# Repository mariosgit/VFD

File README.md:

# VFD

A collection of upcycling projects for Vakuum Fluorescent Displays (VFD). These are Display as you may find in Audio/Video gear like CD/DVD players. A VFD requires high voltage to control anodes and gates, and a small AC voltage for the fillament(heater). To drive each single display element, a time multiplexed controller is required.

## Project Structure...

This is a playground for testing VFDs and there are the PCBs in PCB-KiCAD. See below..

If you only want the display drivers, check out the external repos which are submoduled in the ```./lib``` folder.

```lib/...``` containes submodule display libs and maybe some other local libs which are in development. If a stable status is reached I move them into their own repo.

```src/VFD_TPIC..``` stuff was not integrated into this platformio project yet..

```src/PanelDemo``` is a simple example for a VFD + encoder and button inputs.

```src/FreeDSPController``` is like PanelDemo + it reads some data via I2C from a FreeDSP/ADSP1701. It's a first experiment to use the code generated by SigmaStudio.

### Software Testing

So this is "just" a wrapper PlatformIO project which allows quick switching between the displays I work on.

The thing to be build can be choosen in ```.env``` file. If there is none, copy the ```.env.example```.

### src/main

Is a wrapper into the other sources under ```src``` or into the examples under ```lib/XYZ/examples/...```.

You can also switch between demo programms by commenting in/out the defines.. only one at a time... but using ```.env``` does not infect the git repo.

## PCBs

There are some sub-schematics like VFD-Power which are included in the other schematics.

### MN12832JC-TeensyLC

This is a VFD + 2 Encoders + 2 Switches. (For the FreeDSPController)

Status: Works somewhat, It would have been better with Level shifters. During power up it can show some random noise, due to level issues.

### GP1294AI

This is a board with the VFD + 2 encoders + 10 switches.

#### Status: Experimental, PCB is in development. 

Has some bugs, I2C and I2S on wrong pins... etc.

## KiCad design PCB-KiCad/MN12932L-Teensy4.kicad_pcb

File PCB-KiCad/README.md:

# PCB's

### Reminder

To edit a schematic/pcb, open the .pro file first (double click) KiCad needs this to handle sch/pcb together, otherwise u get wiered errors when updating pcb from schematic.

## GP1294 panel

| front | back |
|---|---|
|  |  |
| | |

A Panel with that display and an Teensy4.

Intended Use: Graphical EQ. The bottom PCB is a FreeDSP-AllInOne.
 * Infopage https://freedsp.github.io/
 * Github: https://github.com/freeDSP/freeDSP-ALLinONE 

Contains
* Power for VFD (~3V fillament, 30-50V for anode and grid) and 5V for other stuff.
* Teensy4 - Controls the Amp and shows vintage spectrum analyser.
* 2 Encoders
* 5 Buttons.

### Status

Tested, has bugs... Can be patched to work somewhat.

### Bugs

* VFD pin 9 (TEST) must have 100k pullup to 3.3V and small buffer C.✅
* SDA/SCL are twisted ! ✅
* PL(atch) is not connected to ATTiny ! Removed ATTiny ✅
* ATTiny fliegt raus, zu umstaendlich.✅
* I2S pins wrong, fixed + SRCs ✅
* 5V reg wrong footprint (from a kicad lib)
* Add revision info
* Crosscheck wiring with proto

### Bugs

* RECOM 5V reg wrong footprint (from a kicad lib)
* VFD pin 9 (TEST) must have 100k pullup to 3.3V and small buffer C.

### Todo

* Test audio connection to/from teensy I2S slave ! Can it do USB playback ? T3.2 or T4.0 ?

* FreeDSP-AIO flaws ✅
  * speaker mute before shutdown...
    * it has a startup unmute circuit but no shutdown...
    * [One more7414 gate and 2 diodes and 2 resistors...](https://www.falstad.com/circuit/circuitjs.html?ctz=CQAgjCAMB0l3BWEAmM0EE4DMGAcB2ZLMSANjABYxkQFTbbJaBTAWjDACgA3EV-XBXCkmrQbmFMmEElOgQpUdJwBKfcZPUZ6YEVHAppNavpgJOAB3W6UyIWJvJcErKc5hcr1lgTH89VmRCcH9TdHBoUnosaCxXJEh3Tz4fGm0+ILT6OSQ0KJAYuIZEjy9UkAo4DODKxTMI-ML4qE4Adz4wUJt2ExtE9sC7YQ6u7M4AcxH6XFFO+nSpTgBjKeH2UJn9ZDYJCmgMbREOHAO8SgTYSC4AJ1XWCgl1nWzweDg21bn1aVDE26eQgEvnZFLJ4MtViDVlhIEImNsxBV9rgMP4sKQMHRILhkNglHAuJMATD7F8sMg6h9BkIoQCof1IZUOiZ6VSvl9AsEvgzqWtyn0qfyAuUFpZqjRauKKqQhK5FlYehKqorpbK3ANMiB0pzjE4WhquXrvL5wHqefyjfzflTkENaeVWQMHUzjUrFhT8B16JKmHFvSAALYAVwALsxOB6pRyKRJKEIhABBAMWVgAegAogA5COQT0OZ6iZxMB4VEAANQAlgA7AAU1ECFDLAEoc3nCPCXaQhhwJYGAIYWAA6AGdh0GLBYADYATxHZZHIYA9iOEGWqbhHEN85o-nx2ygXfuSfoZu8iUfYXuKQVr4sBvvaaQ6Af5Xwn-RH8-j3KWqU+AhQlpCh0npJRckiaJYmaHkH2xK8O1fe4QJdYDvSqH8eVtWVL2JS9MLtYJeVZP97nJPgS1dciJByBpIKKBIxRVWkewKS8MMFE17keDkSx5CgyKAsiuP1O5qG40JhMSAATKVJXYDA3RQEApOYAAzPsg0nENOBknUKm1MAFP0j9lLUjStLZEw5MMxSeRsiplXs1CRNIiVtX4mhWQVGUqLfWUaHYgYfOEgFJNbUSjQo3RixAAAFRdWmYa4AHkq3CyiQuPVh0iEAArINhxDEc+xHAALZhJwsJKF2XYdxmYIrh1XdKAI-F1fFjUIhArAMA2YKSKz7MMRwsBLquHKSEqrEcVLDJYQwrRc0sjeS3ICTYEAoeMQGSlQR0XVSRrG65JtaabhwAHyOxLrnHdKeMeTZsv9YdJwS67xvHGaGuYebFrS-53xff9AKZaRwQGZzBM8sH3C7L0HNmb1NhoFT1M0kNWEnfqDAUfFCQRh4keMtx-hsayrKqJgEHeSGyOcvTnJg68WP4QRwBMGD2dZgQhGi398HsfcedIWMjIgGn4HxDAqDeOX4BoFRmGHCtCr7KslnDe9Rc0Nm+b0RJF0MG99AADw3K4aAuPGkCQCRUH0JBWE22gbelJTwdoALqIYQIsE4I2KACmgmHNkgWTkGRSwSAoY4ge4JR-J36dcOVYAYoA) ... voltage divider at the schmitt input set to trigger when Vin goes below 8V or so !? then OR that output via 2 diodes into the spk_sleep. Adjust: turn pot from full (cw) towards 0 (ccw) until the mute LED goes off.
    * tested ✅
  * Not much capacitance at Vin, more caps ! Could delay the shutdown ! More time to mute ! ✅

## MN12832L panel

| front | back |
|---|---|
|  |  |
| | |

Eurorack 24U format - 12cm width. Made for some very specific recycled receiver knobs.

### Status

Batch v0.1 ordered.

### BOM

| "Id" | "Designator" | "Footprint" | "Quantity" | "Designation" |
| --- | --- | --- | --- | --- |
| 15 | "U3,U4" | "SOIC-16_3.9x9.9mm_P1.27mm" | 2 | "74HC165" |  |  | 
| 34 | "U1" | "MN12832L" | 1 | "~" |  |  | 
| 30 | "U2" | "Teensy4.0" | 1 | "~" |  |  | 
| 23 | "U5" | "Converter_DCDC_RECOM_R-78E-0.5_THT" | 1 | "R-78B5.0-2.0" |  |  | 
| 29 | "IC2" | "SO8" | 1 | "ZXBM5210" |  |  | 
| 17 | "IC1" | "SO14" | 1 | "74132D" |  |  | 
| 18 | "IC3" | "TO263-5" | 1 | "XL6009" |  |  | 
|  2 | "D5,D4,D3,D2" | "D_SOD-123" | 4 | "1N4448W" |  |  | 
| 16 | "D1" | "D_SOD-123" | 1 | "1N5818" |  |  | 
| 14 | "L1" | "L_Cenker_CKCS5020" | 1 | "SM-NE45" |  |  | 
| 22 | "L2" | "L_Cenker_CKCS8040" | 1 | "22uH" |  |  | 
|  1 | "C1" | "C1206" | 1 | "4.7n" (FF-Freq) |  |  | 
| 10 | "C4" | "CP_Elec_6.3x5.8" | 1 | "47u/35v" |  |  | 
| 12 | "C6" | "CP_Elec_6.3x5.8" | 1 | "4.7u/100v" |  |  | 
| 13 | "C3,C5" | "C_1210_3225Metric_Pad1.33x2.70mm" | 2 | "1u/100v" |  |  | 
| 33 | "C2" | "C_0603_1608Metric_Pad1.08x0.95mm" | 1 | "1u" |  |  | 
|  4 | "R2,R1" | "R_0603_1608Metric_Pad0.98x0.95mm" | 2 | "2.7k" (R2-FF-Freq) |  |  | 
|  5 | "RN4,RN3,RN1,RN2" | "R_Array_SIP5" | 4 | "R_Network04" |  |  | 
| 25 | "R14,R13" | "R_0603_1608Metric" | 2 | "2.2k" |  |  | 
| 11 | "R6" | "R_Axial 10mm" | 1 | "91k" |  |  | 
| 24 | "R4" | "R_Axial_DIN0207_L6.3mm_D2.5mm_P10.16mm" | 1 | "91k" VoltReg |  |  | 
| 31 | "R5" | "R_Axial_DIN0207_L6.3mm_D2.5mm_P10.16mm" | 1 | "2k" | |  | 
|  9 | "R3" | "0411_15" | 1 | "22" 5W |  |  | 
| 35 | "SW3,SW2,SW1,SW4,SW5" | "RotaryEncoder_Alps_EC11E" | 5 |  |  |  | 

# Refs

Used Kicad 3d models:
 * models https://gitlab.com/MountyRox/kicad-packages3D.git 
 * sources https://gitlab.com/kicad/libraries/kicad-packages3D-source.git

# Reminders

Start more Kicad instances on MacOS:
```
open -n -a "kicad"
```

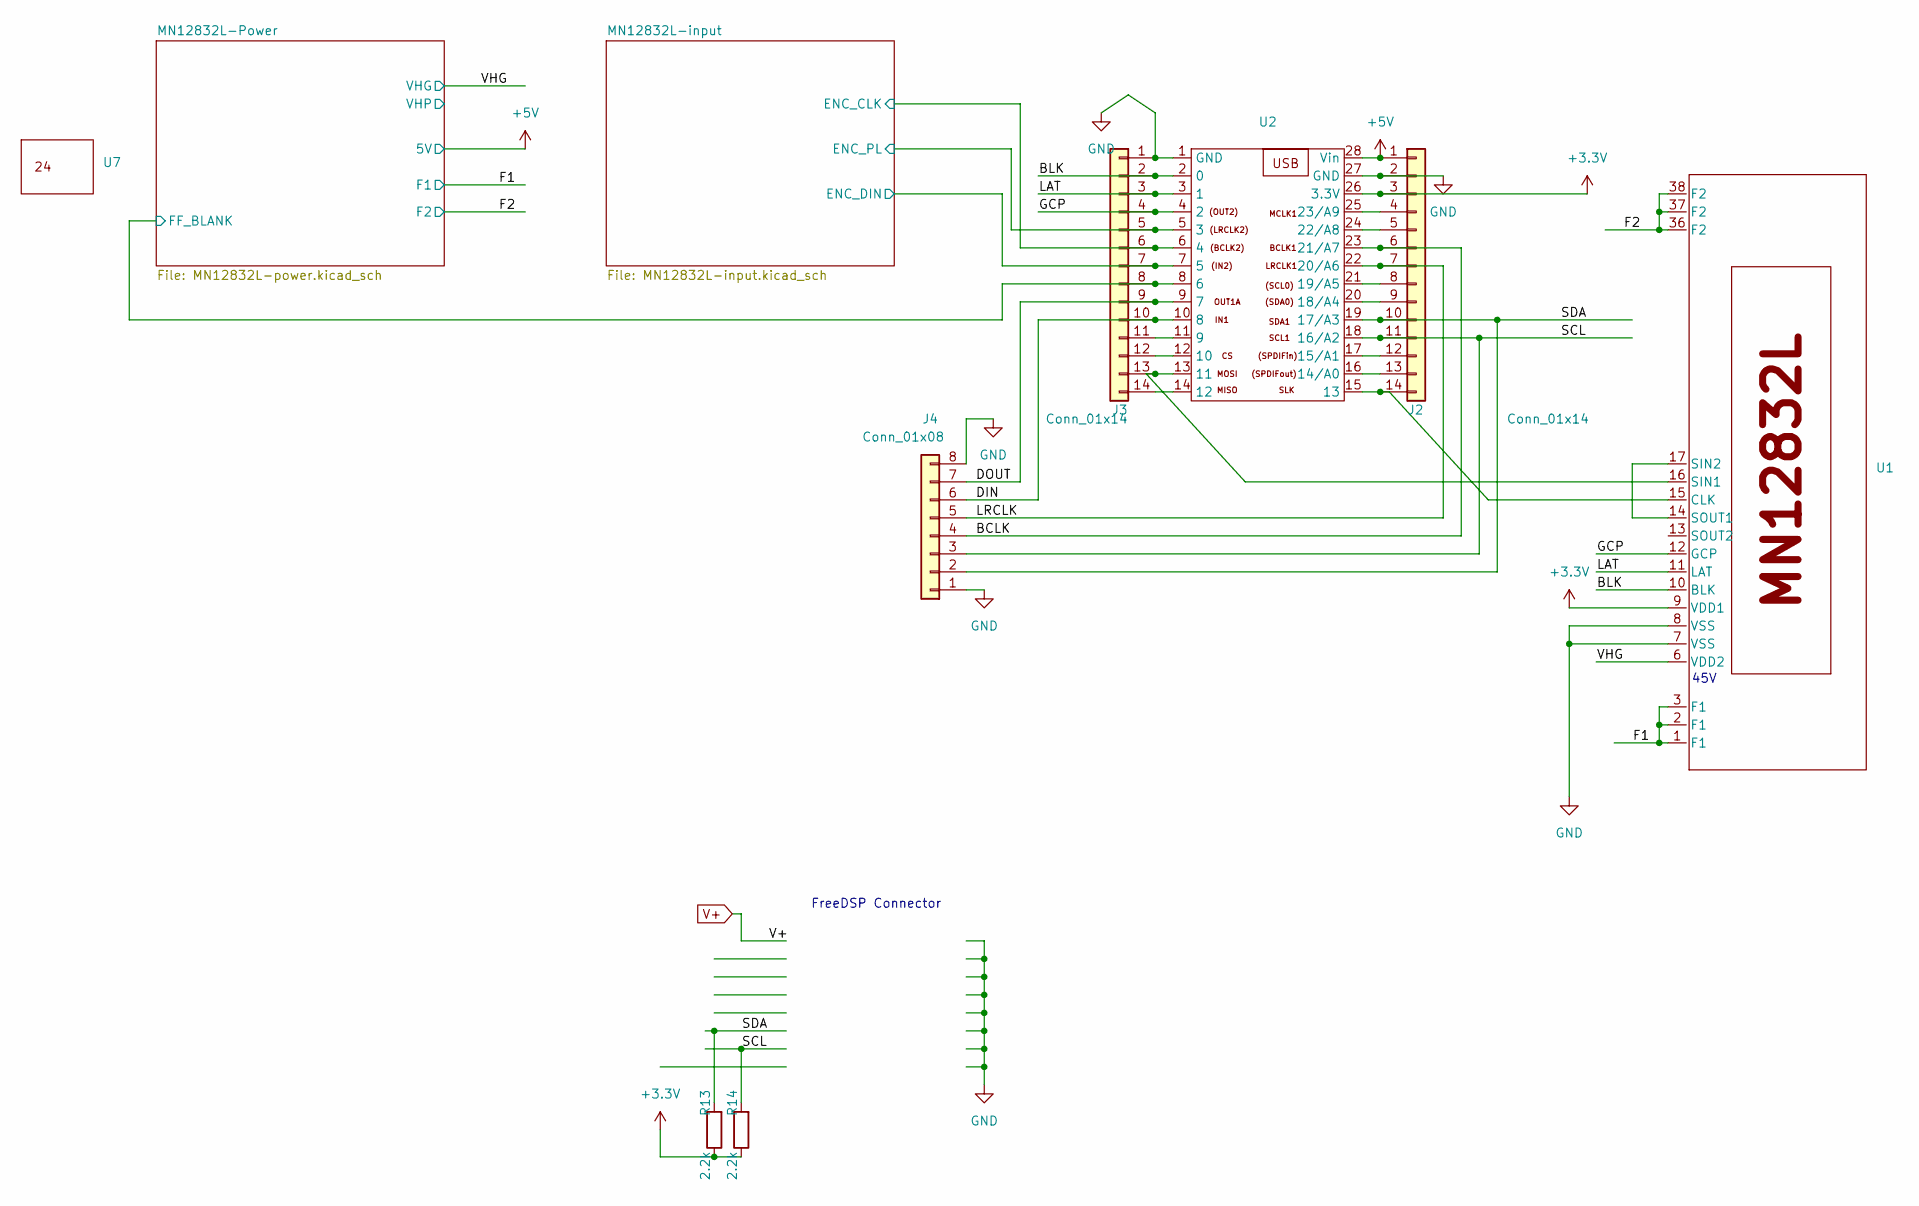
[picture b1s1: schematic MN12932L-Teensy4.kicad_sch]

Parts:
J2, J3: Conn_01x14; PinSocket_1x14_P2.54mm_Vertical
J4: Conn_01x08; PinSocket_1x08_P2.54mm_Vertical
R13, R14: 2.2k; R_0603_1608Metric
U1: MN12832L
U2: Teensy4.0
U7: MN12832L-Front24

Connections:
+3.3V: J2.3, R13.1, R14.1, U1.9 (VDD1), U2.26 (3.3V); also elsewhere on the board
+5V: J2.1, U2.28 (Vin); also elsewhere on the board
/BCLK: J2.6, J4.4, U2.23 (21/A7)
/BLK: J3.2, U1.10 (BLK), U2.2 (0)
/DIN: J3.10, J4.6, U2.10 (8)
/DOUT: J3.9, J4.7, U2.9 (7)
/GCP: J3.4, U1.12 (GCP), U2.4 (2)
/LAT: J3.3, U1.11 (LAT), U2.3 (1)
/LRCLK: J2.7, J4.5, U2.22 (20/A6)
/MN12832L-input/ENC_CLK: J3.6, U2.6 (4); also elsewhere on the board
/MN12832L-input/ENC_DIN: J3.7, U2.7 (5); also elsewhere on the board
/MN12832L-input/ENC_PL: J3.5, U2.5 (3); also elsewhere on the board
/SCL: J2.11, J4.3, R14.2, U2.18 (16/A2)
/SDA: J2.10, J4.2, R13.2, U2.19 (17/A3)
F1: U1.1 (F1), U1.2 (F1), U1.3 (F1); also elsewhere on the board
F2: U1.36 (F2), U1.37 (F2), U1.38 (F2); also elsewhere on the board
FF_BLANK: J3.8, U2.8 (6); also elsewhere on the board
GND: J2.2, J3.1, J4.1, J4.8, U1.7 (VSS), U1.8 (VSS), U2.1 (GND), U2.27 (GND); also elsewhere on the board
unnamed: J2.4, U2.25 (23/A9)
unnamed: J2.5, U2.24 (22/A8)
unnamed: J2.8, U2.21 (19/A5)
unnamed: J2.9, U2.20 (18/A4)
unnamed: J2.12, U2.17 (15/A1)
unnamed: J2.13, U2.16 (14/A0)
unnamed: J2.14, U1.15 (CLK), U2.15 (13)
unnamed: J3.11, U2.11 (9)
unnamed: J3.12, U2.12 (10)
unnamed: J3.13, U1.16 (SIN1), U2.13 (11)
unnamed: J3.14, U2.14 (12)
unnamed: U1.14 (SOUT1), U1.17 (SIN2)
VHG: U1.6 (VDD2); also elsewhere on the board

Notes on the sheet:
FreeDSP Connector
45V

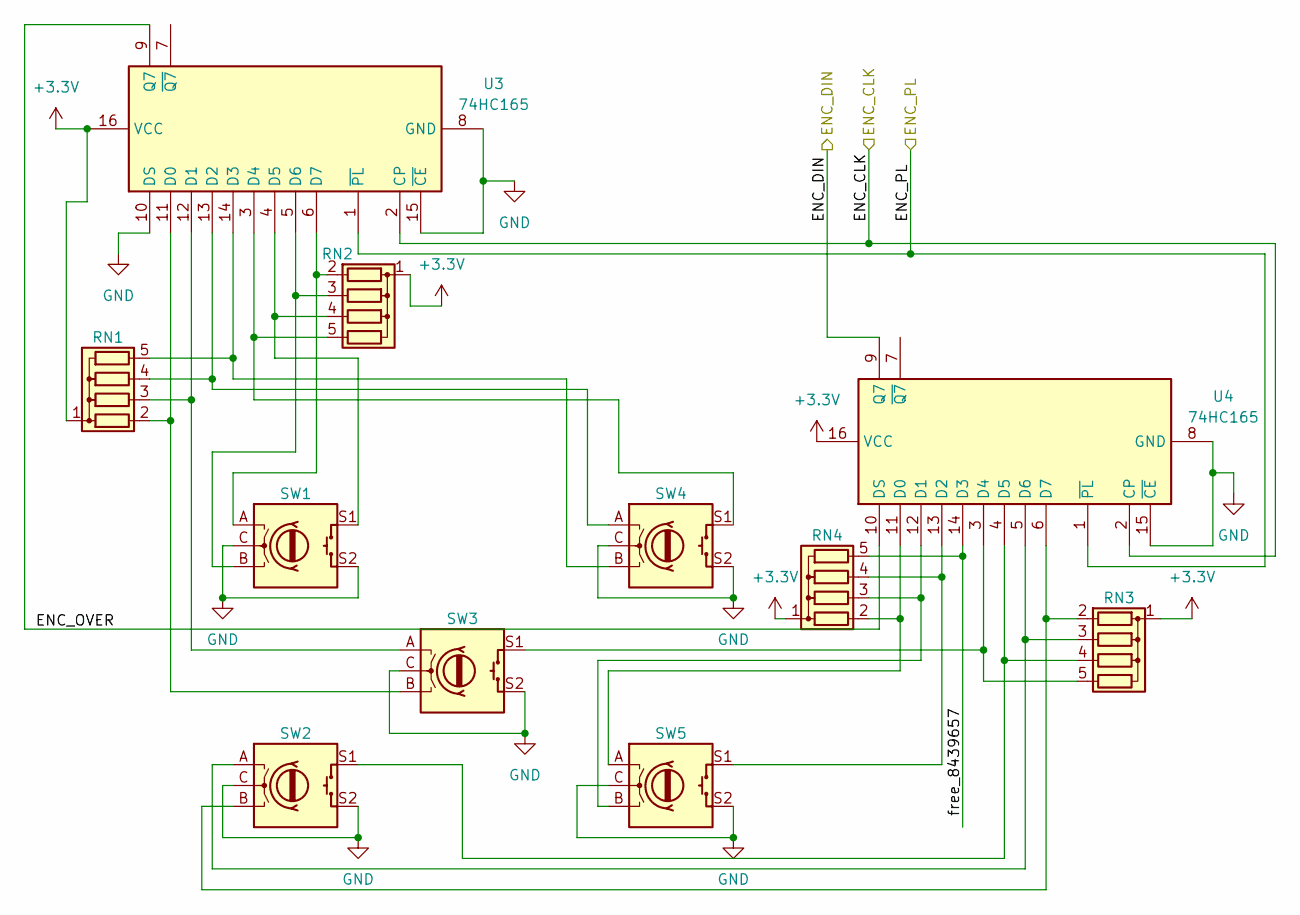
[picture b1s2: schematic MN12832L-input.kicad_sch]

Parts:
RN1, RN2, RN3, RN4: R_Network04; R_Array_SIP5
SW1, SW2, SW3, SW4, SW5: RotaryEncoder_Switch; RotaryEncoder_Alps_EC11E-Switch_Vertical_Centered
U3, U4: 74HC165; SOIC-16_3.9x9.9mm_P1.27mm

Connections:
+3.3V: RN1.1 (common), RN2.1 (common), RN3.1 (common), RN4.1 (common), U3.16 (VCC), U4.16 (VCC); also elsewhere on the board
/MN12832L-input/ENC_CLK: U3.2 (CP), U4.2 (CP); also elsewhere on the board
/MN12832L-input/ENC_DIN: U4.9 (Q7); also elsewhere on the board
/MN12832L-input/ENC_OVER: U3.9 (Q7), U4.10 (DS)
/MN12832L-input/ENC_PL: U3.1 (~PL), U4.1 (~PL); also elsewhere on the board
/MN12832L-input/free_8439657: RN4.5 (R4), U4.14 (D3)
GND: SW1.C, SW1.S2, SW2.C, SW2.S2, SW3.C, SW3.S2, SW4.C, SW4.S2, SW5.C, SW5.S2, U3.8 (GND), U3.10 (DS), U3.15 (~CE), U4.8 (GND), U4.15 (~CE); also elsewhere on the board
unnamed: RN1.2 (R1), SW3.B, U3.11 (D0)
unnamed: RN1.3 (R2), SW3.A, U3.12 (D1)
unnamed: RN1.4 (R3), SW4.A, U3.13 (D2)
unnamed: RN1.5 (R4), SW4.B, U3.14 (D3)
unnamed: RN2.2 (R1), SW1.A, U3.6 (D7)
unnamed: RN2.3 (R2), SW1.B, U3.5 (D6)
unnamed: RN2.4 (R3), SW1.S1, U3.4 (D5)
unnamed: RN2.5 (R4), SW4.S1, U3.3 (D4)
unnamed: RN3.2 (R1), SW2.B, U4.6 (D7)
unnamed: RN3.3 (R2), SW2.A, U4.5 (D6)
unnamed: RN3.4 (R3), SW2.S1, U4.4 (D5)
unnamed: RN3.5 (R4), SW3.S1, U4.3 (D4)
unnamed: RN4.2 (R1), SW5.A, U4.11 (D0)
unnamed: RN4.3 (R2), SW5.B, U4.12 (D1)
unnamed: RN4.4 (R3), SW5.S1, U4.13 (D2)

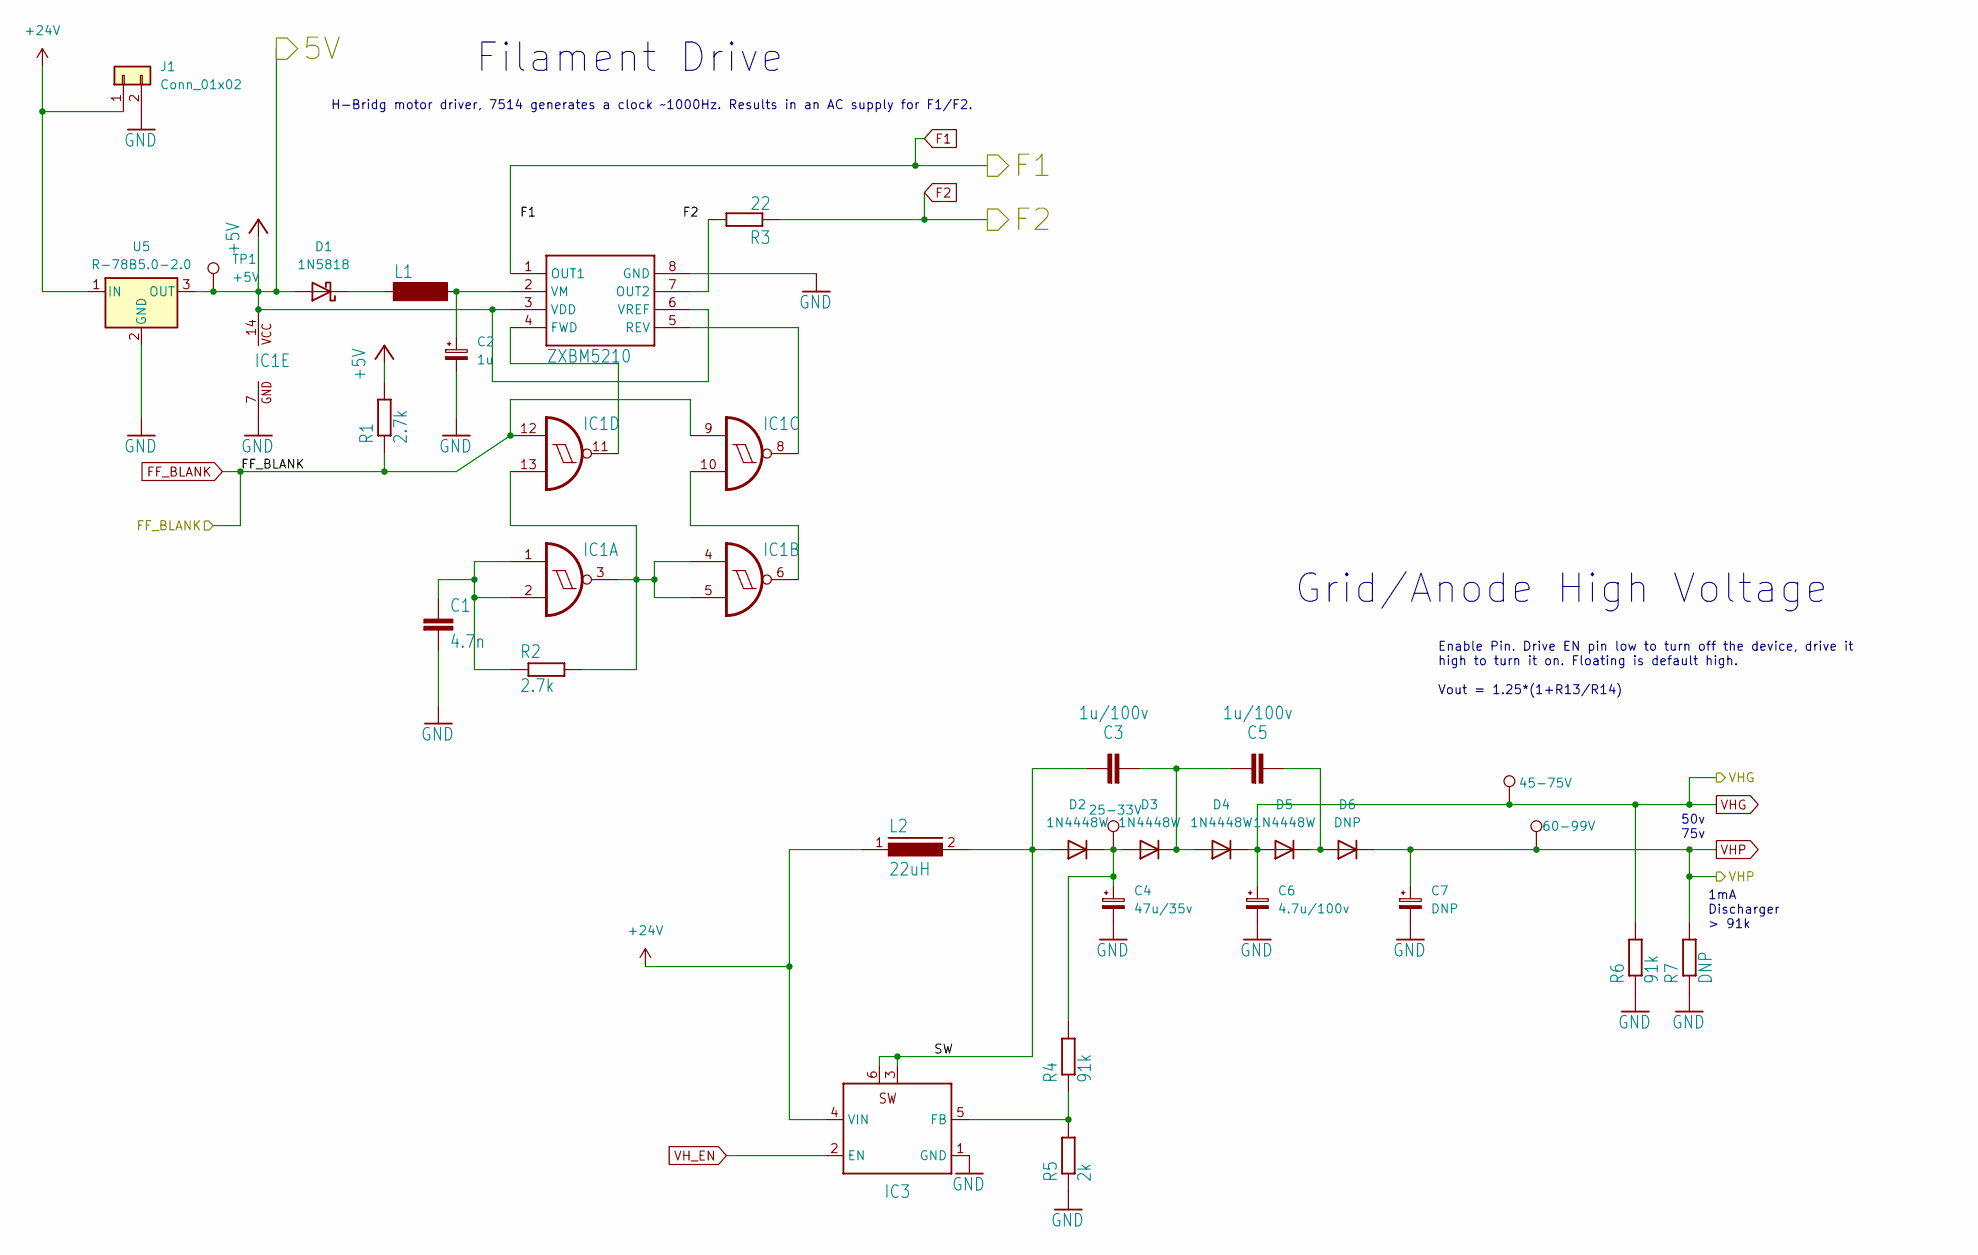
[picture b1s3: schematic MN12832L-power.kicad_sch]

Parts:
C1: 4.7n; C1206
C2: 1u; C_0603_1608Metric_Pad1.08x0.95mm_HandSolder
C3, C5: 1u/100v; C_1210_3225Metric_Pad1.33x2.70mm_HandSolder
C4: 47u/35v; CP_Elec_6.3x5.8
C6: 4.7u/100v; CP_Elec_6.3x5.8
C7: DNP; CP_Elec_6.3x5.8
D1: 1N5818; D_SOD-123
D2, D3, D4, D5: 1N4448W; D_SOD-123
D6: DNP; D_SOD-123
IC1: 74132D; SO14
IC2: ZXBM5210; SO8
IC3: TO263-5
J1: Conn_01x02; TerminalBlock_Phoenix_MKDS-1,5-2-5.08_1x02_P5.08mm_Horizont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
L1: SM-NE45; L_Cenker_CKCS5020
L2: 22uH; L_Cenker_CKCS8040
R1, R2: 2.7k; R_0603_1608Metric_Pad0.98x0.95mm_HandSolder
R3: 22; 0411_15
R4: 91k; R_Axial_DIN0207_L6.3mm_D2.5mm_P10.16mm_Horizontal
R5: 2k; R_Axial_DIN0207_L6.3mm_D2.5mm_P10.16mm_Horizontal
R6: 91k; R_0603_1608Metric_Pad0.98x0.95mm_HandSolder
R7: DNP; R_0603_1608Metric_Pad0.98x0.95mm_HandSolder
TP1: +5V; TestPoint_Pad_2.0x2.0mm
TP2: 25-33V; TestPoint_Pad_2.0x2.0mm
TP3: 45-75V; TestPoint_Pad_2.0x2.0mm
TP4: 60-99V; TestPoint_Pad_2.0x2.0mm
U5: R-78B5.0-2.0; Converter_DCDC_RECOM_R-78E-0.5_THT

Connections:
+5V: D1.2 (A), IC1.14 (VCC), IC2.3 (VDD), IC2.6 (VREF), R1.2, TP1.1, U5.3 (OUT); also elsewhere on the board
+24V: IC3.4 (VIN), J1.1, L2.1, U5.1 (IN)
/MN12832L-Power/SW: C3.1, D2.2 (A), IC3.3 (SW), IC3.6 (SW@1), L2.2
F1: IC2.1 (OUT1); also elsewhere on the board
F2: R3.1; also elsewhere on the board
FF_BLANK: IC1.9 (I0), IC1.12 (I0), R1.1; also elsewhere on the board
GND: C1.2, C2.2, C4.2, C6.2, C7.2, IC1.7 (GND), IC2.8 (GND), IC3.1 (GND), J1.2, R5.1, R6.1, R7.1, U5.2 (GND); also elsewhere on the board
unnamed: D1.1 (K), L1.1
unnamed: C4.1, D2.1 (K), D3.2 (A), R4.2, TP2.1
unnamed: C3.2, C5.1, D3.1 (K), D4.2 (A)
unnamed: C5.2, D5.1 (K), D6.2 (A)
unnamed: C1.1, IC1.1 (I0), IC1.2 (I1), R2.1
unnamed: IC1.3 (O), IC1.4 (I0), IC1.5 (I1), IC1.13 (I1), R2.2
unnamed: IC1.6 (O), IC1.10 (I1)
unnamed: IC1.8 (O), IC2.5 (REV)
unnamed: IC1.11 (O), IC2.4 (FWD)
unnamed: IC2.7 (OUT2), R3.2
unnamed: C2.1, IC2.2 (VM), L1.2
unnamed: IC3.5 (FB), R4.1, R5.2
VHG: C6.1, D4.1 (K), D5.2 (A), R6.2, TP3.1; also elsewhere on the board
VHP: C7.1, D6.1 (K), R7.2, TP4.1
VH_EN: IC3.2 (EN)

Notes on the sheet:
H-Bridg motor driver, 7514 generates a clock ~1000Hz. Results in an AC supply for F1/F2.
Filament Drive
50v 75v
Grid/Anode High Voltage
Enable Pin. Drive EN pin low to turn off the device, drive it high to turn it on. Floating is default high. Vout = 1.25*(1+R13/R14)
1mA Discharger > 91k

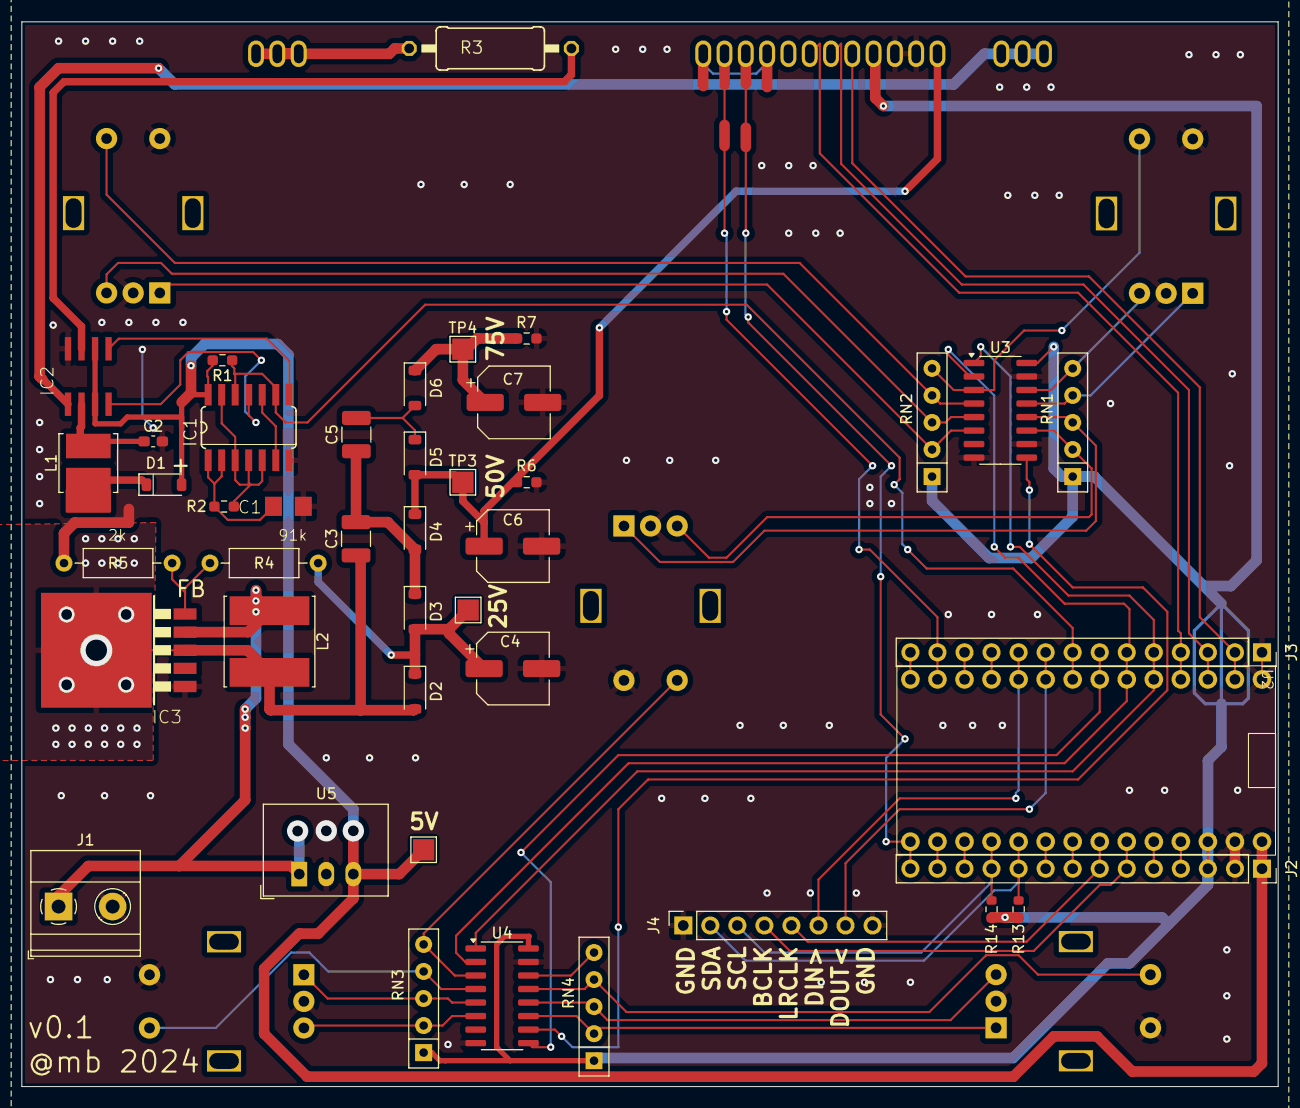
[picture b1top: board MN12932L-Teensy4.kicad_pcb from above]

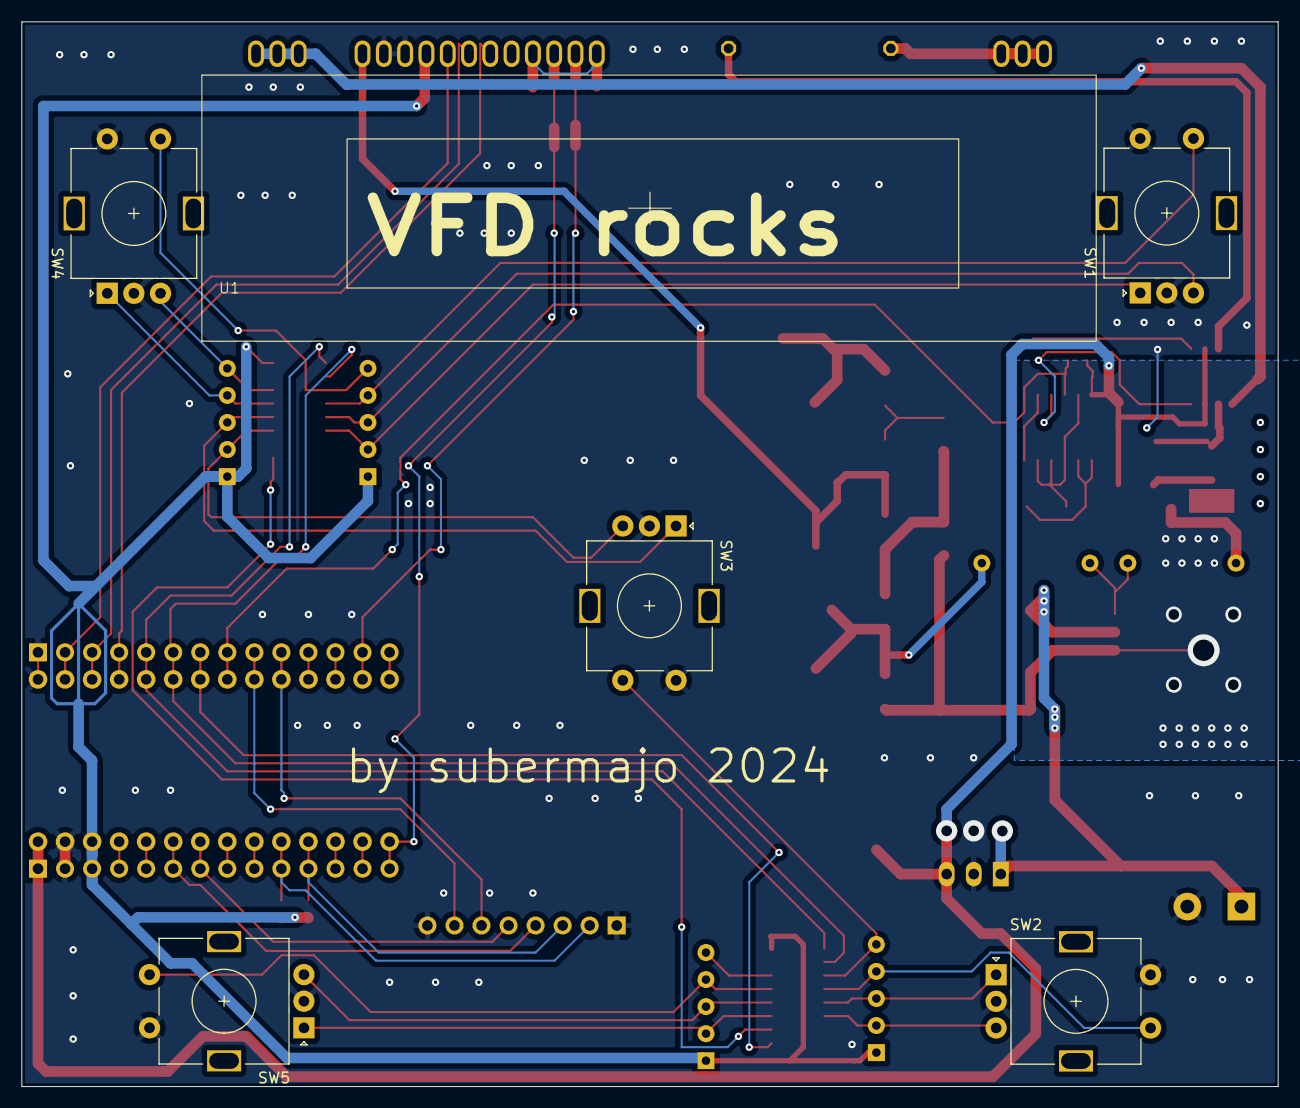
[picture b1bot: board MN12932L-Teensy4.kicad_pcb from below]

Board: 2 copper layers, 118.0 x 100.0 mm, 50 parts (6 on the bottom side), 63 nets.

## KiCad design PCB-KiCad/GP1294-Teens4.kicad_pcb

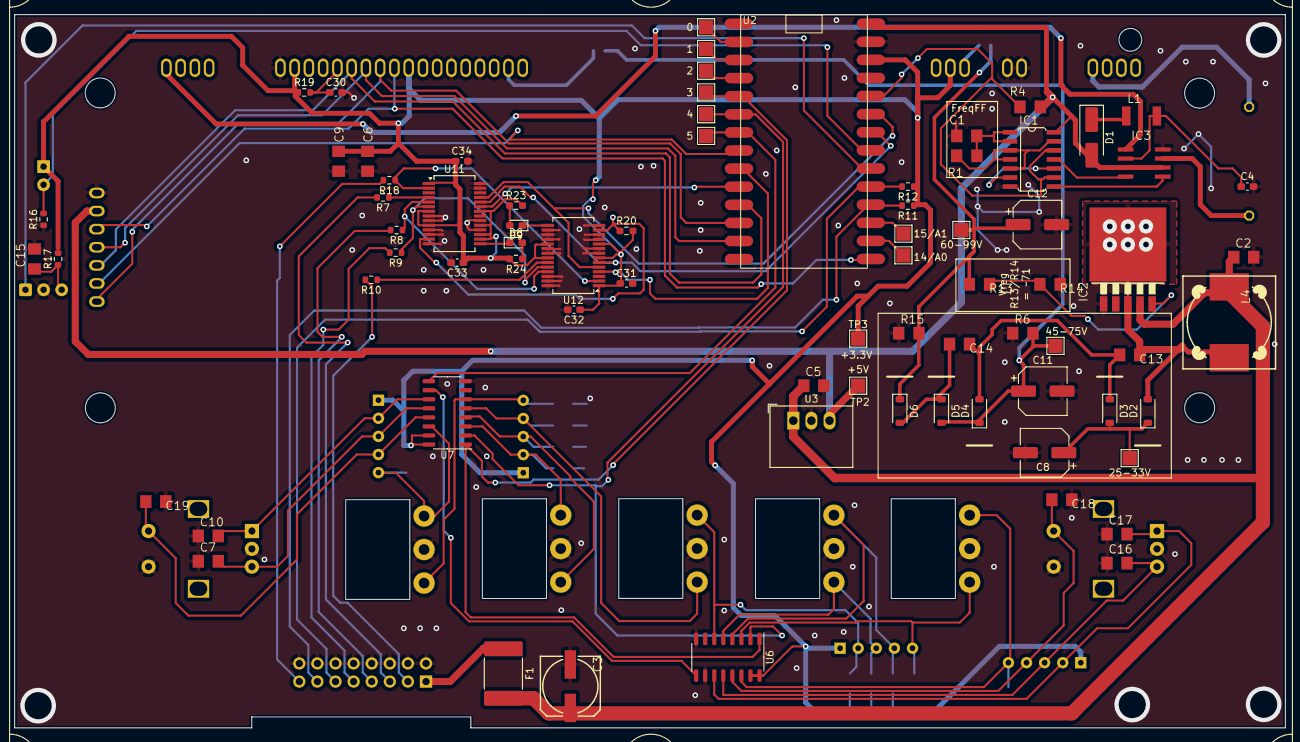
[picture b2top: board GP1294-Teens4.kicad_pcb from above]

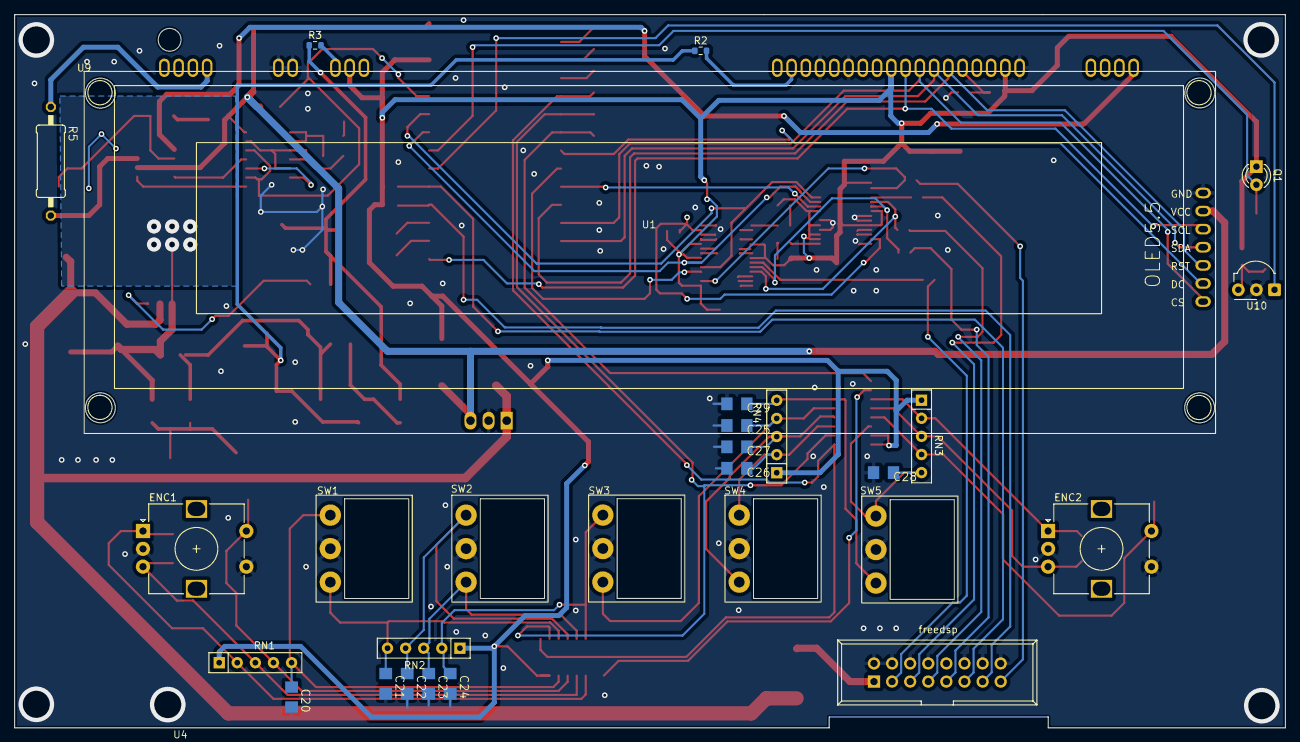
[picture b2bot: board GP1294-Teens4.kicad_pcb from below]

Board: 2 copper layers, 178.3 x 100.1 mm, 106 parts (29 on the bottom side), 80 nets.

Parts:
C1: 4.7n; C1206
C2, C6, C15: 100n; C1206
C3: 10u; 153CLV-0807
C4: 1u; C_0603_1608Metric_Pad1.08x0.95mm_HandSolder
C5: C-EUC1206; C1206
C7, C10, C16, C17, C18, C19, C20, C21, C22, C23, C24, C25, C26, C27, C28, C29: 10n; C1206
C8: 47u/35v; CP_Elec_6.3x5.8
C9: 1u; C1206
C11, C12: 4.7u/100v; CP_Elec_6.3x5.8
C13, C14: 1u/100v; C1206
C30, C31, C33: 100n; C_0603_1608Metric_Pad1.08x0.95mm_HandSolder
C32, C34: 10u; C_0603_1608Metric_Pad1.08x0.95mm_HandSolder
Case1: CaseDD
D1: 1N5818; D_SMA_Handsoldering
D2, D3, D4, D5, D6: 1N4448W; D_SOD-123
D8: rdy-in; LED_0603_1608Metric_Pad1.05x0.95mm_HandSolder
D9: rdy-out; LED_0603_1608Metric_Pad1.05x0.95mm_HandSolder
ENC1, ENC2: RotaryEncoder_Switch; RotaryEncoder_Alps_EC12E-Switch_Vertical_H20mm
F1: Polyfuse; Fuse_2920_7451Metric_Pad2.10x5.45mm_HandSolder
IC1: 74132D; SO14
IC2: TO263-5
IC3: ZXBM5210; SO8
L1: SM-NE45
L4: 22uH; DR125
Q1: ALS-PDIC144; LED_D3.0mm_Clear
R1, R4: 2.7k; R1206
R2, R3: 10; R_0603_1608Metric
R5: 22; 0411_15
R6, R13, R15: 91k; R1206
R7, R8, R9, R10, R17, R18: 100; R_0603_1608Metric
R11, R12: 2.2k; R_0603_1608Metric
R14: 2k; R1206
R16: 5.1k; R_0603_1608Metric
R19: 100k; R_0603_1608Metric
R20: 10k; R_0603_1608Metric_Pad0.98x0.95mm_HandSolder
R23, R24: 390; R_0603_1608Metric_Pad0.98x0.95mm_HandSolder
RN1, RN2, RN3, RN4: R_Network04; R_Array_SIP5
SW1, SW2, SW3, SW4, SW5: SW_DPDT_x2; SwitchMS500Ecut
TP1: 45-75V; TestPoint_Pad_2.0x2.0mm
TP2: +5V; TestPoint_Pad_2.0x2.0mm
TP3: +3.3V; TestPoint_Pad_2.0x2.0mm
TP4: 14/A0; TestPoint_Pad_2.0x2.0mm
TP5: 15/A1; TestPoint_Pad_2.0x2.0mm
TP9: 60-99V; TestPoint_Pad_2.0x2.0mm
TP10: 5; TestPoint_Pad_2.0x2.0mm
TP11: 4; TestPoint_Pad_2.0x2.0mm
TP12: 3; TestPoint_Pad_2.0x2.0mm
TP13: 2; TestPoint_Pad_2.0x2.0mm
TP14: 1; TestPoint_Pad_2.0x2.0mm
TP15: 0; TestPoint_Pad_2.0x2.0mm
TP16: 25-33V; TestPoint_Pad_2.0x2.0mm
U1: GP1294AI
U2: Teensy4.0_smd
U3: R-78B5.0-2.0; Converter_DCDC_RECOM_R-78B-2.0_THT
U4: FreeDSP-allinone
U6, U7: 74HC165; SO-16_3.9x9.9mm_P1.27mm
U9: OLED5.5
U10: TSOP34S40F; Vishay_MOLD-3Pin
U11, U12: SSOP-28_5.3x10.2mm_P0.65mm

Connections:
+3.3V: C6.1, C9.1, C31.1, C32.1, C33.1, C34.1, Q1.1 (C), R11.1, R12.1, R17.2, R19.1, R20.2, R23.2, R24.2, RN1.1 (common), RN2.1 (common), RN3.1 (common), RN4.1 (common), TP3.1, U1.6 (VDD), U1.14 (VDD), U1.24 (VDD), U2.26 (3.3V), U6.15 (~CE), U6.16 (VCC), U7.15 (~CE), U7.16 (VCC), U11.1 (LGRP), U11.7 (VIO), U11.10 (IFMT0), U11.16 (OWL1), U11.17 (OWL0), U11.19 (OFMT0), U11.22 (VDD), U12.1 (LGRP), U12.7 (VIO), U12.10 (IFMT0), U12.19 (OFMT0), U12.22 (VDD)
+5V: D1.2 (A), IC1.14 (VCC), IC3.3 (VDD), IC3.6 (VREF), R4.2, TP2.1, U2.28 (Vin), U3.3 (OUT), U9.2 (VCC)
+24V: C2.1, C3.+, C5.1, F1.2, IC2.4 (VIN), L4.1, U3.1 (IN)
/BCK_OUT: R8.1, U11.5 (BCKI), U12.25 (BCKO)
/BCLK1: U2.23 (21/A7), U11.25 (BCKO), U12.5 (BCKI)
/DATA_OUT: R7.1, U11.4 (SDIN)
/DISP_CS: U1.12 (CS), U2.12 (10), U9.7 (CS)
/DISP_DC: U2.8 (6), U9.6 (DC)
/DISP_RESET: U1.10 (RESET), U2.11 (9), U9.5 (RST)
/IN1: U2.10 (8), U11.23 (SDOUT)
/LRCK_OUT: R9.1, U11.6 (LRCKI), U12.24 (LRCKO)
/LRCLK1: U2.22 (20/A6), U11.24 (LRCKO), U12.6 (LRCKI)
/MOSI: U1.11 (DIO), U2.13 (11), U9.4 (SDA)
/OUT1: U2.9 (7), U12.4 (SDIN)
/SCLK: U1.13 (CLK), U2.15 (13), U9.3 (SCL)
/SRC/To_DSP: R10.1, U12.23 (SDOUT)
/VFD-Power2x/SW: C13.1, D2.2 (A), IC2.3 (SW), IC2.6 (SW@1), L4.2
/inputs/S1: C20.1, RN1.5 (R4), SW1.1 (A), U6.14 (D3)
/inputs/S2: C21.1, RN2.5 (R4), SW1.3 (C), U6.3 (D4)
/inputs/S3: C22.1, RN2.4 (R3), SW2.1 (A), U6.4 (D5)
/inputs/S4: C23.1, RN2.3 (R2), SW2.3 (C), U6.5 (D6)
/inputs/S5: C24.1, RN2.2 (R1), SW3.1 (A), U6.6 (D7)
/inputs/S6: C25.1, RN4.4 (R3), SW3.3 (C), U7.5 (D6)
/inputs/S7: C26.1, RN4.2 (R1), SW4.1 (A), U7.3 (D4)
/inputs/S8: C27.1, RN4.3 (R2), SW4.3 (C), U7.4 (D5)
/inputs/S9: C28.1, RN3.5 (R4), SW5.1 (A), U7.14 (D3)
/inputs/S10: C29.1, RN4.5 (R4), SW5.3 (C), U7.6 (D7)
/inputs/enc1a: C17.2, ENC1.A, RN1.2 (R1), U6.11 (D0)
/inputs/enc1b: C16.2, ENC1.B, RN1.3 (R2), U6.12 (D1)
/inputs/enc1c: C18.2, ENC1.S1, RN1.4 (R3), U6.13 (D2)
/inputs/enc2a: C10.2, ENC2.A, RN3.2 (R1), U7.11 (D0)
/inputs/enc2b: C7.2, ENC2.B, RN3.3 (R2), U7.12 (D1)
/inputs/enc2c: C19.2, ENC2.S1, RN3.4 (R3), U7.13 (D2)
BtnCLK: TP11.1, U2.6 (4), U6.2 (CP), U7.2 (CP)
BtnLAT: TP12.1, U2.5 (3), U6.1 (~PL), U7.1 (~PL)
BtnSIN: TP10.1, U2.7 (5), U7.9 (Q7)
F1: IC3.1 (OUT1), U1.1 (F+)
F2: R5.1, U1.28 (F-)
FF_BLANK: IC1.9 (I0), IC1.12 (I0), R4.1, U2.24 (22/A8)
GND: C1.2, C2.2, C3.-, C4.2, C5.2, C6.2, C7.1, C8.2, C9.2, C10.1, C11.2, C12.2, C15.2, C16.1, C17.1, C18.1, C19.1, C20.2, C21.2, C22.2, C23.2, C24.2, C25.2, C26.2, C27.2, C28.2, C29.2, C30.2, C31.2, C32.2, C33.2, C34.2, ENC1.C, ENC1.S2, ENC2.C, ENC2.S2, IC1.7 (GND), IC2.1 (GND), IC3.8 (GND), R6.1, R14.1, R15.1, R16.1, SW1.2 (B), SW2.2 (B), SW3.2 (B), SW4.2 (B), SW5.2 (B), U1.5 (GND), U1.17 (GND), U1.19 (GND), U1.26 (GND), U1.27 (GND), U2.1 (GND), U2.27 (GND), U3.2 (GND), U4.2 (GND), U4.4 (GND), U4.6 (GND), U4.8 (GND), U4.10 (GND), U4.12 (GND), U4.14 (GND), U4.16 (GND), U6.8 (GND), U6.10 (DS), U7.8 (GND), U9.1 (GND), U10.2 (GND), U11.8 (DGND), U11.9 (BYPAS), U11.11 (IFMT1), U11.12 (IFMT2), U11.14 (MUTE), U11.18 (OFMT1), U11.20 (TDMI), U11.21 (DGND), U11.26 (MODE0), U11.27 (MODE1), U11.28 (MODE2), U12.8 (DGND), U12.9 (BYPAS), U12.11 (IFMT1), U12.12 (IFMT2), U12.14 (MUTE), U12.16 (OWL1), U12.17 (OWL0), U12.18 (OFMT1), U12.20 (TDMI), U12.21 (DGND), U12.26 (MODE0), U12.27 (MODE1), U12.28 (MODE2)
MCLK: R18.1, U11.2 (RCKI), U12.2 (RCKI)
unnamed: D1.1 (K), L1.1
unnamed: C8.1, D2.1 (K), D3.2 (A), TP16.1
unnamed: C13.2, C14.1, D3.1 (K), D4.2 (A)
unnamed: C14.2, D5.1 (K), D6.2 (A)
unnamed: D8.2 (A), R24.1
unnamed: D8.1 (K), U11.15 (/RDY)
unnamed: D9.2 (A), R23.1
unnamed: D9.1 (K), U12.15 (/RDY)
unnamed: C1.1, IC1.1 (I0), IC1.2 (I1), R1.1
unnamed: IC1.3 (O), IC1.4 (I0), IC1.5 (I1), IC1.13 (I1), R1.2
unnamed: IC1.6 (O), IC1.10 (I1)
unnamed: IC1.8 (O), IC3.5 (REV)
unnamed: IC1.11 (O), IC3.4 (FWD)
unnamed: IC2.5 (FB), R13.1, R14.2
unnamed: IC3.7 (OUT2), R5.2
unnamed: C4.1, IC3.2 (VM), L1.2
unnamed: Q1.2 (E), R16.2, U2.21 (19/A5)
unnamed: C30.1, R19.2, U1.9 (TEST)
unnamed: R2.2, U1.21 (VHG)
unnamed: R3.2, U1.25 (VHP)
unnamed: TP15.1, U2.2 (0)
unnamed: TP14.1, U2.3 (1)
unnamed: TP13.1, U2.4 (2)
unnamed: TP4.1, U2.16 (14/A0)
unnamed: TP5.1, U2.17 (15/A1)
unnamed: R18.2, U4.15 (MCLK)
unnamed: R10.2, U4.3 (MP1/MDI)
unnamed: R7.2, U4.5 (MP8/MDO)
unnamed: R9.2, U4.9 (MP10/LRCLK)
unnamed: R8.2, U4.7 (MP11/BCLK)
unnamed: U6.9 (Q7), U7.10 (DS)
unnamed: U2.20 (18/A4), U10.1 (OUT)
unnamed: C15.1, R17.1, U10.3 (Vs)
RST: R20.1, U11.13 (/RST), U12.13 (/RST)
SCL: R11.2, U2.18 (16/A2), U4.13 (SCL)
SDA: R12.2, U2.19 (17/A3), U4.11 (SDA)
V+: F1.1, U4.1 (V+)
VHG: C11.1, D4.1 (K), D5.2 (A), R2.1, R6.2, TP1.1
VHP: C12.1, D6.1 (K), R3.1, R13.2, R15.2, TP9.1

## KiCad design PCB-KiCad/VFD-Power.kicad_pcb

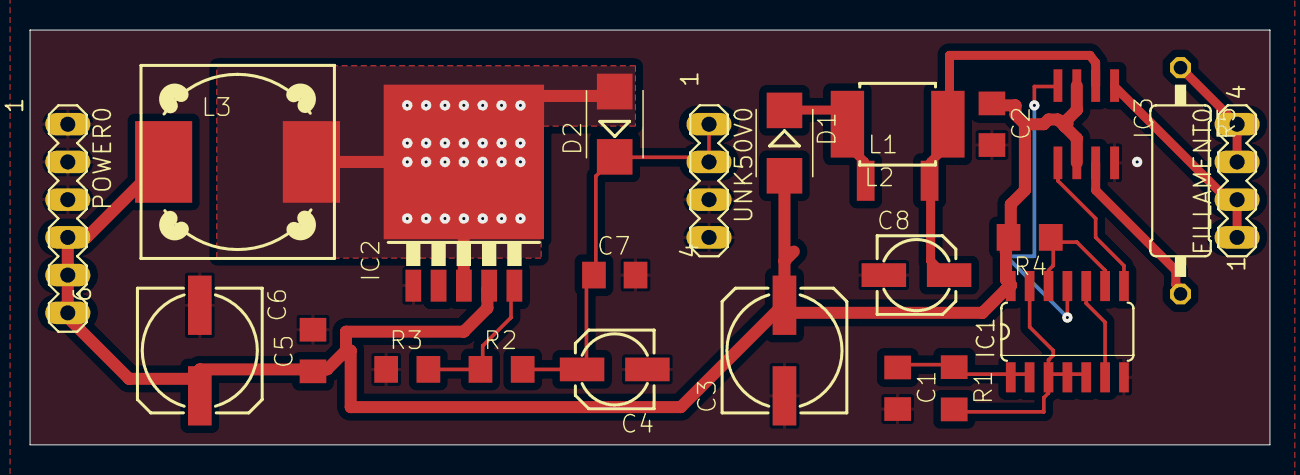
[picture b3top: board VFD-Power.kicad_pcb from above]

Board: 2 copper layers, 83.5 x 27.9 mm, 24 parts (0 on the bottom side), 16 nets.

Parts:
C1: 4.7n; C1206
C2, C7: 100n; C1206
C3: 10u; 153CLV-0807
C4, C8: 1u; 153CLV-0505
C5: C-EUC1206; C1206
C6: CPOL-EU153CLV-0807; 153CLV-0807
D1, D2: DIODE-SMB; SMB
FILLAMENT0: MA04-1
IC1: 74132D; SO14
IC2: XL6009; TO263-5
IC3: ZXBM5210; SO8
L1: SM-NE45
L2: MS85
L3: DR125
POWER0: MA06-1
R1, R4: 2.7k; R1206
R2: 1.5k; R1206
R3: 39; R1206
R5: 22; 0411_15
UNK50V0: MA04-1

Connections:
+5V: C2.1, C3.+, C5.1, C6.+, D1.A, IC1.14 (VCC), IC2.4 (VIN), IC3.3 (VDD), IC3.6 (VREF), L3.1, POWER0.4, POWER0.5, POWER0.6, R4.2
/F1: FILLAMENT0.1, FILLAMENT0.2, IC3.1 (OUT1)
/F2: FILLAMENT0.3, FILLAMENT0.4, R5.1
/FF_BLANK: IC1.9 (I0), IC1.12 (I0), R4.1
/SW: D2.A, IC2.3 (SW), IC2.6 (SW@1), L3.2
GND: C1.2, C2.2, C3.-, C4.-, C5.2, C6.-, C7.2, C8.-, IC1.7 (GND), IC2.1 (GND), IC3.8 (GND), POWER0.1, POWER0.2, POWER0.3, R3.1, UNK50V0.3, UNK50V0.4
unnamed: D1.C, L1.1, L2.1
unnamed: C1.1, IC1.1 (I0), IC1.2 (I1), R1.1
unnamed: IC1.3 (O), IC1.4 (I0), IC1.5 (I1), IC1.13 (I1), R1.2
unnamed: IC1.6 (O), IC1.10 (I1)
unnamed: IC1.8 (O), IC3.5 (REV)
unnamed: IC1.11 (O), IC3.4 (FWD)
unnamed: IC2.5 (FB), R2.1, R3.2
unnamed: IC3.7 (OUT2), R5.2
unnamed: C8.+, IC3.2 (VM), L1.2, L2.2
VPP: C4.+, C7.1, D2.C, R2.2, UNK50V0.1, UNK50V0.2
